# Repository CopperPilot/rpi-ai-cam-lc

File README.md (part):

# Compact CM5 AI Camera

Compute Module 5 6-layer carrier board (55x40 mm) with 12MP AI Camera rotated 90 deg on 8 mm spacers, 50 mm fold-under 15-pin FFC on CAM0, USB-C PD/flashing, 2x USB-A 2.0, full-size HDMI, and snap-fit two-part FDM enclosure assembled by Lion Circuits

Generated from photos with [rea-hardware](https://github.com/CopperPilot/rea-hardware): KiCad schematic and PCB, enclosure, manufacturing files, and a gated test suite.

| Front | Rear | Exploded |
|---|---|---|
|  |  |  |

**Build video:** [docs/build-video.mp4](docs/build-video.mp4). Assembly order and insertion paths come from `rea/spec.yaml`, the same ones the collision tests check.

## Verification

Verdict **PASS**: 45 pass, 3 warn, 0 fail, 0 error, 0 skipped (generated 2026-11-04T23:04:28Z).

| Gate | Status | Detail |
|---|---|---|
| `spec.valid` Scope contract rea/spec.yaml is complete and consistent | PASS | must_match=8, blocks=5, placements=17, purchased=6, enclosure_parts=4, assembly_steps=11, requirements=8, prompt_chars=9 |
| `inputs.present` Input images and prompt are inside the workspace | PASS | images=6 |
| `brand.clean` No third-party brand marks in names, silkscreen, case or docs | PASS | hits=0 |
| `scope.board_fits` Every board fits inside the product's rounded outline, inside its wall | PASS | boards=1 |
| `sourcing.bom` Every placed part has a live, in-stock part at the fab's parts source | PASS | placed_symbols=81, unique_parts=37, lion_in_house=3, bom_cost_inr=22308.98 |
| `kicad.erc` Schematic ERC: 0 errors | PASS | errors=0, warnings=0 |
| `kicad.drc` PCB DRC with schematic parity + zone refill: 0/0/0 | WARN | errors=0, warnings=300, unconnected=0, parity=0 |
| `kicad.rules` Project rules are no looser than the fab profile; nothing silenced | PASS | fab=lioncircuits, copper_layers=6, tracks=1093, vias=179 |
| `board.contract` Board outline, holes and user-facing parts match the spec | PASS | width_mm=55.0, height_mm=40.0 |
| `kicad.models` Every placed footprint has a 3D model on disk | PASS | lcsc_models_misplaced=0, footprints=88, missing=0, unresolved=0, tampered=0 |
| `kicad.refs` Modules with a verified reference symbol use it (no hand-drawn pinouts) | PASS |  |
| `board.antenna` A module's printed antenna sits at the board edge with nothing around it | PASS |  |
| `kicad.parts` Every part sits on the footprint of that exact LCSC part, with its real 3D model (no placeholders) | WARN | parts=81, lcsc_codes=34, wrong_footprint=0, placeholders=0 |
| `board.cable_pinout` Both ends of each board-to-board cable carry the same signal on each wire | PASS |  |
| `board.stackup` The board's layer count, thickness and stackup match the spec and the fab | PASS | stack_mm:main=1.65 |
| `board.high_speed` Declared high-speed groups (DDR, MIPI, USB) are routed, length-matched and on target impedance | PASS |  |
| `board.user_ports` Every receptacle a person plugs into sits behind a case opening | PASS | user_receptacles:main=4 |
| `board.cc_protection` USB-C CC lines are not clamped to VBUS by a rail-referenced ESD array | PASS |  |
| `board.ground_pins` No ground pin is left unconnected | PASS |  |
| `board.pd_autonomous` A USB-PD charging input negotiates with no processor running | PASS |  |
| `board.connector_mating` Every connector mates from a known side, toward its cable, with a clear mating zone in its footprint | PASS | connectors:main=13 |
| `board.height_zones` Parts under an overhead part stay below the zone's height limit | PASS |  |
| `board.port_facing` Every user-facing port's connector opens towards its case opening (3D model) | PASS |  |
| `review.design` Datasheet-level design review (CopperPilot validate): no open P0 or P1 findings | PASS |  |
| `mech.meshes` Enclosure parts exist, are closed solids, and fit the envelope | PASS |  |
| `mech.openings` Every front/rear/edge feature has an opening in the shell, at its size | PASS | features_tested=7 |
| `mech.assembly` Draft assembly: no collisions seated or along insertion paths | PASS | parts=11, pairs=55, sweep_hits=0, min_clearance_mm=0.0 |
| `mech.dfm` Each enclosure part is manufacturable by its process (walls, build size) | PASS |  |
| `fidelity.dims` Key proportions (bezel, edge and centre thickness, overall size) match the reference | PASS | overall_width=59.0, overall_height=44.0, overall_depth=27.5, edge_thickness=27.5, center_thickness=27.5, corner_radius=5 |
| `integration.assembly` Final assembly with the KiCad-exported PCBA: no collisions | PASS | parts=11, pairs=55, sweep_hits=0, min_clearance_mm=0.0 |
| `integration.cables` Every cable joins two real connectors and fits its route in every pose | PASS | cables=1 |
| `integration.actuators` Every button, crown, dial or sensor window physically works its part | PASS |  |
| `integration.ports` Every port opening has its connector right behind it (a plug can mate) | PASS | ports_tested=4 |
| `integration.mating` Every connector faces what mates with it, and every mounting hole sits on a boss (checked on the 3D models) | PASS | checked=9 |
| `integration.band` A wrist band closes round the wrist, its sensor faces the wrist, and a slide-on charger meets its contacts | PASS |  |
| `integration.retention` Every assembled part is held in place by something real (snap, clip, screw, adhesive, press fit, captured) | PASS |  |
| `integration.rf` A radio's antenna is not sealed inside metal (an RF window exists) | PASS |  |
| `integration.battery_fill` In a laptop- or tablet-sized product the battery fills the free space at its height | PASS |  |
| `integration.camera_view` Every camera sees out: its whole field of view clears the case | PASS |  |
| `fab.package` Gerbers, drill, BOM and CPL exist and agree with the PCB | WARN | bom_lines=34, placements=81, gerber_files=18 |
| `video.build` 3D build video exists and actually shows motion | PASS | seconds=48.0, frames=1440, moving_fraction=0.95 |
| `tests.integrity` Generated test suite is the rea template, unmodified | PASS |  |
| `fidelity.judge` Independent visual judge: renders match the reference photos | PASS | score=9.0, features=8, requirements_score=9 |
| `spec.locked` Scope contract unchanged since scope (or changes justified) | PASS | changed_keys=0 |
| `system.valid` System spec: modules, interfaces, power tree, assembly order are consistent | PASS |  |
| `system.modules` Every built module passes all of its own gates | PASS |  |
| `system.assembly` Modules do not collide with each other, seated or along system insertion paths | PASS |  |
| `system.cables` Every inter-module cable plugs into a real port on each module and is long enough | PASS |  |

Run them yourself: `pip install rea-hardware[video]` then `make test` (one pytest case per gate).

## Bill of materials

33 lines; full file: `fab/rpi-ai-cam-lc-bom.csv`.

| Designators | Part | LCSC |
|---|---|---|
| C1 | 2.2uF |  |
| C8,C10,C11,C12,C34 | 1uF |  |
| C2,C3,C19 | 22uF |  |
| C4,C5,C6,C7,C20,C21,C25,C33 | 100nF |  |
| C22,C23,C24 | 4.7nF |  |
| C26,C27,C28,C29,C30,C31 | 100uF |  |
| C9,C32 | 2.2uF |  |
| D1,D2,D3 | USBLC6-2SC6 |  |
| D5,D6,D7,D9,D10,D11 | TPD1E05U06DPYR |  |
| D12 | BAT54S |  |
| D4 | TVS2200DRVR |  |
| D8 | PESD3V3S1BLYL |  |
| J1 | USB4105-GF-A |  |
| J2,J3 | 629104190121 |  |
| J4 | 10029449-111RLF |  |
| J5 | SFW15R-1STE1LF |  |
| J6,J7 | 10164227-1001A1RLF |  |
| R1,R2,R16 | 43k |  |
| R6,R7,R10,R11 | 22k |  |
| R12 | 390k |  |
| R13 | 49.9k |  |
| R14 | 107k |  |
| R8,R9,R15,R20 | 100k |  |
| R5,R17,R18 | 1.33k |  |
| R19 | 6.8k |  |
| SP1,SP2,SP3,SP4 | 9774080243R |  |
| SP5,SP6,SP7,SP8 | 9774015960R |  |
| SW1 | PTS526SM15SMTR2LFS |  |
| SW2 | B3U-1000P |  |
| U1 | TPD12S016PWR |  |
| U2,U3 | AP2553W6-7 |  |
| U4,U5 | TPS259470ARPWR |  |
| U6 | TPD6S300ARUKR |  |

Off-board parts:

- **cm5**: Compute Module 5 with eMMC (any eMMC variant such as CM5104016 or CM5104032; bought outside Lion Circuits, excluded from the Lion PCBA BOM, and pressed into J6/J7 at final assembly)  (https://www.raspberrypi.com/products/compute-module-5/)
- **ai_camera**: 12 MP IMX500 Intelligent Vision Camera Module SC1174 (https://www.lioncircuits.com/parts)
- **m2_washers**: Eight flat M2 x 0.5 mm nylon washers (two per spacer, 1.0 mm stack height, OD 4.0 mm, ID 2.2 mm) placed atop SP1..SP4  (https://www.mcmaster.com/90295A080/)
- **camera_m2_screws**: Four Essentra M2 x 4 mm pan-head nylon screws fastening ai_camera through m2_washers into SP1..SP4 50M020040N003 (https://www.lioncircuits.com/parts)
- **m25_inserts**: Four M2.5 x 3.5 mm brass heat-set threaded inserts (OD 3.5 mm) pressed into back_shell corner bosses  (https://www.mcmaster.com/94180A321/)
- **m25_screws**: Four M2.5 x 8 mm pan-head machine screws passing from carrier top through SP5..SP8 and the module into m25_inserts  (https://www.mcmaster.com/92000A065/)

## Manufacture

Fab profile: `lioncircuits`, 6 layers, 1.6 mm. Upload `fab/*-gerbers.zip`, then the BOM and CPL CSVs for assembly. Print the enclosure STLs in `case/out/` (fdm).

## Rebuild

```
make all      # case, fab, renders, video, tests, README
make test     # gates only
```

## Scope

- In scope: camera lens window, power button, boot pinhole, USB-C power and flashing port, HDMI port, USB 2.0 Type-A host port 0, USB 2.0 Type-A host port 1, rear CM5 cooling vents
- Out of scope: tripod mount thread, external Wi-Fi u.FL antenna, SD card slot, 40-pin GPIO expansion header
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
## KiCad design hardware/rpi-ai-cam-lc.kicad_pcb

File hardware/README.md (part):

# Compact CM5 AI Camera Carrier (`hardware/rpi-ai-cam-lc`)

Generated from `rea/spec.yaml` by rea-hardware (Lion Circuits Custom tier fab rules, 6-layer 1.6 mm controlled-impedance stack-up, 55.0 x 40.0 mm board outline at origin, mounting holes), then completed and routed for the Compute Module 5 carrier.

## Programming and Debug Path (`decisions`)
- **eMMC Flashing (`rpiboot` over USB-C J1):**
  1. Press and hold recessed boot button `SW2` (Omron `B3U-1000P`, actuated via the front-shell pinhole `F3`), which pulls CM5 `nRPIBOOT` (`J6` pad 93) to `GND` (using CM5's internal `10 kOhm` pull-up to `+3V3` with no redundant external pull-up, and 3.3 V `PESD3V3S1BLYL` ESD TVS `D8` to `GND`).
  2. Connect a host PC to USB-C receptacle `J1` (`USB4105-GF-A`). `J1` supplies `VBUS_IN` (decoupled by `C1` = 2.2 uF and `C4` = 100 nF = `2.3 uF` nominal `cSink` <= 10 uF and protected by TI `TVS2200DRVR` 22 V flat-clamp unidirectional WSON-6 surge TVS `D4` with $V_{\text{RWM}} = 22\text{ V}$ for 20 V USB-C fault tolerance, $V_{\text{CLAMP}} = 27.2\text{ V}$ typ / $27.7\text{ V}$ max at 24 A and $27.6\text{ V}$ typ / $28.0\text{ V}$ max at 40 A $8/20\,\mu\text{s} \le +28\text{ V}$ abs max, and $V_F = -0.5\text{ V}$ typ) via wide `F.Cu` copper polygons, a dedicated 1 oz (`0.035 mm`) `In3.Cu` `VBUS_IN` plane, and 8 parallel `VBUS_IN` vias into two parallel TI `TPS259470ARPWR` active-current-limiting ideal-diode / OVP eFuses (`U4` primary, `U5` secondary; combined $R_{\text{ON(typ)}} = 14.15\text{ m}\Omega$ at $25^\circ\text{C}$ / $21.0\text{ m}\Omega$ max at $85^\circ\text{C}$, mirror-symmetric 9-via `U4.6`/`U5.6` output arrays, 1 oz `In3.Cu` `PWR_5V_PLANE` `/+5V`, and 5 parallel `+5V` vias with `0.50 mm` `B.Cu` bus bars at `J6` pads 77-87 -> `~2 mOhm` total PCB copper+via resistance and `~48 mV` typ / `~110 mV` max carrier drop at 3.0 A) driving all six CM5 `+5v_(Input)` pins (`J6` pads 77, 79, 81, 83, 85, 87). `U4` soft-starts via `C22` = 4.7 nF (`0.43 V/ms`, `~11.7 ms` ramp) so the CM5's internal PMIC input capacitance and carrier `+5V` bulk capacitance (`C30` = 100 uF, `C31` = 100 uF, `C9` = 2.2 uF, `C10..C12` = 3 x 1.0 uF) are isolated from `J1` at hot-plug while `U4`'s open-drain `AUXOFF` holds `U5` `EN/UVLO` low until `U4` achieves full gate overdrive, and `U5`'s open-drain `AUXOFF` (`U5.3`) connects to CM5 `PMIC_Enable` (`J6` pad 99, net `PMIC_ENABLE`) per TI Figure 8-18 to hold the CM5 PMIC in reset until both `U4` and `U5` have completed soft-start and reached full gate overdrive; `C23`/`C24` = 4.7 nF on `U4.10`/`U5.10` (`ITIMER`) set steady-state $t_{\text{ITIMER}} = 3.94\text{ ms}$. `J1` routes `USB2_P`/`USB2_N` directly (through inline ESD array `D1` at `J1`, with `D1` pin 5 on `VBUS_D1_CLAMP` locally decoupled to `GND` by `C25` = 100 nF) to CM5 USB 2.0 OTG (`J7` pads 5/3, CM5 pins 105/103), with `USB_OTG_ID` (`J7` pad 1, CM5 pin 101) left unconnected so the CM5's internal pull-up selects USB Device / `rpiboot` bootloader mode.
  3. The CM5 ROM bootloader enumerates over USB 2.0 OTG for `rpiboot` mass-storage flashing. During reset and `rpiboot`, `22 kOhm` pull-down `R10` holds `USB_VBUS_EN` (`J7` pad 11) at `0 V` so USB-A switches `U2` and `U3` remain disabled and isolated from `J1`.
- **UART0 Debug Console:**
  - Exposed on top-side 1.0 mm SMD test pads `TP1` (`UART0_TXD` / `GPIO14`, `J6` pad 55), `TP2` (`UART0_RXD` / `GPIO15`, `J6` pad 51), and `TP3` (`GND`), referenced to `+3V3` (`GPIO_VREF` on `J6` pad 78 strapped to `+3V3`).

## Component Voltage, Current, and Pinout Rating Checks
- **USB-C `cSink` Margin, Parallel `TPS259470ARPWR` Soft-Start / OVP Stage & Capacitor Voltage Ratings (>= 1.5x max rail voltage):**
  - `C1` (`CL21B225KBYNNWE`, LCSC `C6534398`, Samsung 2.2 uF 50 V 0805 X7R): rated **50 V** on `VBUS_IN` at `J1` (**1.79x margin** above `D4` `TVS2200DRVR` 28.0 V max 40 A 8/20 us clamping voltage and **2.38x margin** above continuous 21.0 V USB-C PD overvoltage faults).
  - `C9`, `C32` (`GRM188Z71E225KE43D`, 2.2 uF 0603 X7R): rated **25 V** on switched **5.0 V** (`+5V` bulk decoupling at `J6` and `PMIC_ENABLE` blanking filter `C32`, 5.0x margin).
  - `C4` (`GRM155R71H104KE14D`, 100 nF 0402 X7R): rated **50 V** on **5.0 V** (`VBUS_IN` high-frequency bypass at `J1`, 10.0x margin).
  - Total unswitched capacitance on `VBUS_IN` upstream of `U4`/`U5` is `C1` (2.2 uF) + `C4` (0.1 uF) = **2.3 uF nominal** (**2.53 uF max** at +10% tolerance, well below the `<= 10 uF` USB Type-C `cSink` limit).
  - **Parallel `TPS259470ARPWR` Ideal-Diode / OVP Stage (`U4`, `U5`, LCSC `C3662799`):** Configured per TI `TPS25947` Datasheet Section 8.2.7 / Figure 8-18 ("Two Devices Connected in Parallel for Higher Steady State Current Capability"):
    - Primary eFuse `U4` soft-starts via `C22` = `4.7 nF` 50 V X7R 0402 (`GRM155R71H472KA01D`, LCSC `C77024`) on pin 7 (`DVDT`), setting output ramp slew rate $\text{SR} = 2\,\mu\text{A} / 4.7\text{ nF} = 0.426\text{ V/ms}$ ($t_{\text{ramp}} \approx 11.7\text{ ms}$ to 5.0 V), limiting hot-plug charging current into the CM5 and carrier `+5V` capacitance (`C30` = 100 uF, `C31` = 100 uF, `C9` = 2.2 uF, `C10..C12` = 3 x 1.0 uF) while `U4` pin 3 (`AUXOFF`, open-drain) holds `U5` pin 1 (`EN/UVLO`, net `VBUS_U5_EN`) low.
    - Once `U4` completes inrush and reaches full HFET gate overdrive, `U4.3` (`AUXOFF`) goes high-Z and the divider `R15` = `100 kOhm` (referenced to upstream `VBUS_IN` to `VBUS_U5_EN`) / `R16` = `43 kOhm` (`VBUS_U5_EN` to `GND`) biases `U5.1` (`EN/UVLO`) to `1.50 V` at `5.0 V` (setting $V_{\text{IN(UVLO\_R)}} = 3.99\text{ V}$ and $V_{\text{IN(UVLO\_F)}} = 3.66\text{ V}$ without sensitivity to downstream `+5V` load droop), turning `U5` fully ON in parallel with `U4` for a combined $R_{\text{ON(typ)}} = 28.3\text{ m}\Omega / 2 = 14.15\text{ m}\Omega < 15\text{ m}\Omega$ (`42.5 mV < 0.05 V` drop at 3.0 A) and integrated reverse-current blocking; open-drain `U5` pin 3 (`AUXOFF`), `U4` pin 4 (`~{FLT}`), and `U5` pin 4 (`~{FLT}`) on net `VBUS_AUXOFF` feed CM5 `PMIC_Enable` (`J6` pad 99, net `PMIC_ENABLE`, internally pulled up to `+5V` via `100 kOhm` on CM5) through `R19` = `6.8 kOhm` (`RC0402FR-076K8L`, LCSC `C93940`), `C32` = `2.2 uF` 25 V X7R 0603 (`GRM188Z71E225KE43D`, LCSC `C415535` to `GND`, $C_{\text{eff}} \ge 1.85\,\mu\text{F}$ typ / $1.68\,\mu\text{F}$ min at 5 V bias and -10% tolerance, setting $\tau_{\text{fall}} = 14.0\text{ ms}$ nominal / $10.7\text{ ms}$ worst-case derated $> 2.7\times t_{\text{ITIMER}} = 3.94\text{ ms}$ so a $3.94\text{ ms}$ low pulse keeps `PMIC_ENABLE` $\ge 3.58\text{ V} \gg 2.0\text{ V}$ $V_{\text{IH(min)}}$, and $V_{\text{LOW}} = 0.37\text{ V} < 0.40\text{ V}$ $V_{\text{IL(max)}}$), external pull-up `R5` = `1.33 kOhm` (`RC0402FR-071K33L` from `+5V` to `VBUS_AUXOFF`), and dual series Schottky diode `D12` (`Rectron BAT54S`, LCSC `C408389`: Diode 1 Pin 1->3 from `VBUS_AUXOFF` to `PMIC_ENABLE` providing fast charge $\tau_{\text{rise}} = 2.88\text{ ms}$ nominal / $2.42\text{ ms}$ effective so `PMIC_ENABLE` slews $0.4\text{ V}\to 2.0\text{ V}$ in $1.12\text{ ms}$ and recharges $4.4\times$ faster than $\tau_{\text{fall}}$ without ratcheting while reverse-biasing when `VBUS_AUXOFF` is low, and Diode 2 Pin 3->2 from `PMIC_ENABLE` to `+5V` immediately discharging `C32` into `+5V` so `J6.99` is never back-driven on rapid `+5V` collapse) per TI Figure 8-18 ("To downstream enable").
    - Three-resistor divider `R12` = `390 kOhm` (`RC0402FR-07390KL`, LCSC `C163467`, $\ge 350\text{ k}\Omega$ per datasheet Note 2) / `R13` = `49.9 kOhm` (`RC0402FR-0749K9L`, LCSC `C137969`) / `R14` = `107 kOhm` (`RC0402FR-07107KL`, LCSC `C138070`) from `VBUS_IN` to `GND` sets `U4.1` (`EN/UVLO`) rising threshold to $1.20\text{ V} \times 546.9 / 156.9 = 4.18\text{ V}$ (falling $3.83\text{ V}$) and shared `U4.2`/`U5.2` (`OVLO`) rising threshold to $1.20\text{ V} \times 546.9 / 107 = 6.13\text{ V}$ typ ($5.83\text{ V}$ min $> 5.50\text{ V}$ USB-PD `vSafe5V` max, $6.45\text{ V}$ max; falling $5.62\text{ V}$ typ / $5.33\text{ V}$ min, disconnecting $> 6.1\text{ V}$ and 20 V USB-C faults).
    - `R17` and `R18` = `1.33 kOhm` 1% 0402 (`RC0402FR-071K33L`, LCSC `C276261`, $\ge 750\,\Omega$ UL2367 limit) on `U4.9` and `U5.9` (`ILM`) set $I_{\text{LIM(typ)}} = 2.504\text{ A}$ per channel ($5.00\text{ A}$ combined $\le \text{J1 } 5.0\text{ A}$ VBUS contact rating, $I_{\text{LIM(min)}} = 2.281\text{ A}$, $I_{\text{LIM(max)}} = 2.731\text{ A}$), ensuring neither eFuse reaches $I_{\text{LIM(min)}}$ under worst-case 60%/40% PCB passive current-sharing asymmetry up to $2.281\text{ A} / 0.60 = 3.80\text{ A}$ ($> 3.62\text{ A}$ worst-case system fault load / $3.26\text{ A}$ nominal full load) while active current-limit regulation equalizes sharing up to $5.0\text{ A}$, and `C23` and `C24` = `4.7 nF` 50 V X7R 0402 (`GRM155R71H472KA01D`, LCSC `C77024`) on `U4.10` (`VBUS_U4_ITIMER`) and `U5.10` (`VBUS_U5_ITIMER`) set steady-state transient overcurrent blanking to $t_{\text{ITIMER(typ)}} = 3.94\text{ ms}$ after start-up.
  - `C8`, `C10`, `C11`, `C12`, `C34` (`GRM155R61E105KE11J`, 1 uF 0402 X5R): rated **25 V** on switched **5.0 V** (`HDMI0_5V` output reservoir `C8` and `+5V` local input bypass `C10..C12` at `U2`, `U3`, and `U1` pin 11 `VCC5V`, 5.0x margin) and **3.3 V** (`U6.10` `VPWR` bypass `C34`, 7.6x margin).
  - `C26`..`C31` (`Kemet T520B107M010ATE070`, 100 uF 10 V 70 mOhm Case B 3528-21 `KO-CAP` polymer tantalum, LCSC `C600583`): rated **10 V** (90% recommended operating voltage up to **9.0 V** at $85^\circ\text{C}$ per Kemet T520 datasheet, 2.0x margin on **5.0 V**) with zero DC-bias derating. Two 100 uF polymer tantalum capacitors are placed on `USB0_VBUS` (`C26` at `(3.50, 31.50)`, `C27` at `(25.75, 35.15)`) and two on `USB1_VBUS` (`C28` at `(26.25, 29.55)`, `C29` at `(32.65, 26.80)`), providing **222 uF nominal / ~207.5 uF effective** (`>= 167.5 uF` worst-case at -20% tolerance) per USB 2.0 Type-A host port alongside `C2` and `C3` (`22 uF` 16 V X5R 0603 MLCC, `~7.5 uF` effective at 5 V bias), exceeding the `>= 120 uF` USB 2.0 Section 7.2.4.1 (Table 7-7, $C_{\text{PB}}$) requirement and limiting hot-plug droop into a 10 uF peripheral load to $\le 230\text{ mV} \le 330\text{ mV}$. Charging `207.5 uF` to 5.0 V at `U2`/`U3`'s current limit ($I_{\text{LIM(typ)}} = 0.615\text{ A}$, $I_{\text{LIM(min)}} = 0.56\text{ A}$) takes $1.69\text{ ms}$ typ ($1.85\text{ ms}$ at $0.56\text{ A}$), well within the `AP2553W6-7`'s $7\text{ ms}$ typical ($4\text{--}15\text{ ms}$) fault-blanking timer ($t_{\text{Blank}}$). Two additional 100 uF polymer tantalum capacitors (`C30` at `(32.50, 12.20)`, `C31` at `(32.50, 5.50)`) provide **205.2 uF nominal / ~203.5 uF effective** bulk storage on the switched `+5V` rail alongside `C9` (`2.2 uF`) and `C10..C12` (`3 x 1 uF`), adding only $86\text{ mA}$ during `U4`'s $0.43\text{ V/ms}$ soft-start ramp.
  - `C2`, `C3`, `C19` (`CL10A226MO7JZNC`, Samsung 22 uF 16 V 0603 X5R; alternate `CL10A226MP8NUNE` 10 V X5R 0603): rated **16 V** (or **10 V** alternate) on switched **5.0 V** (`USB0_VBUS` high-frequency bypass on `C2`, `USB1_VBUS` high-frequency bypass on `C3`, >=2.0x margin) and **3.3 V** (`+3V3` camera bulk decoupling at `J5` on `C19`, >=3.0x margin).
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
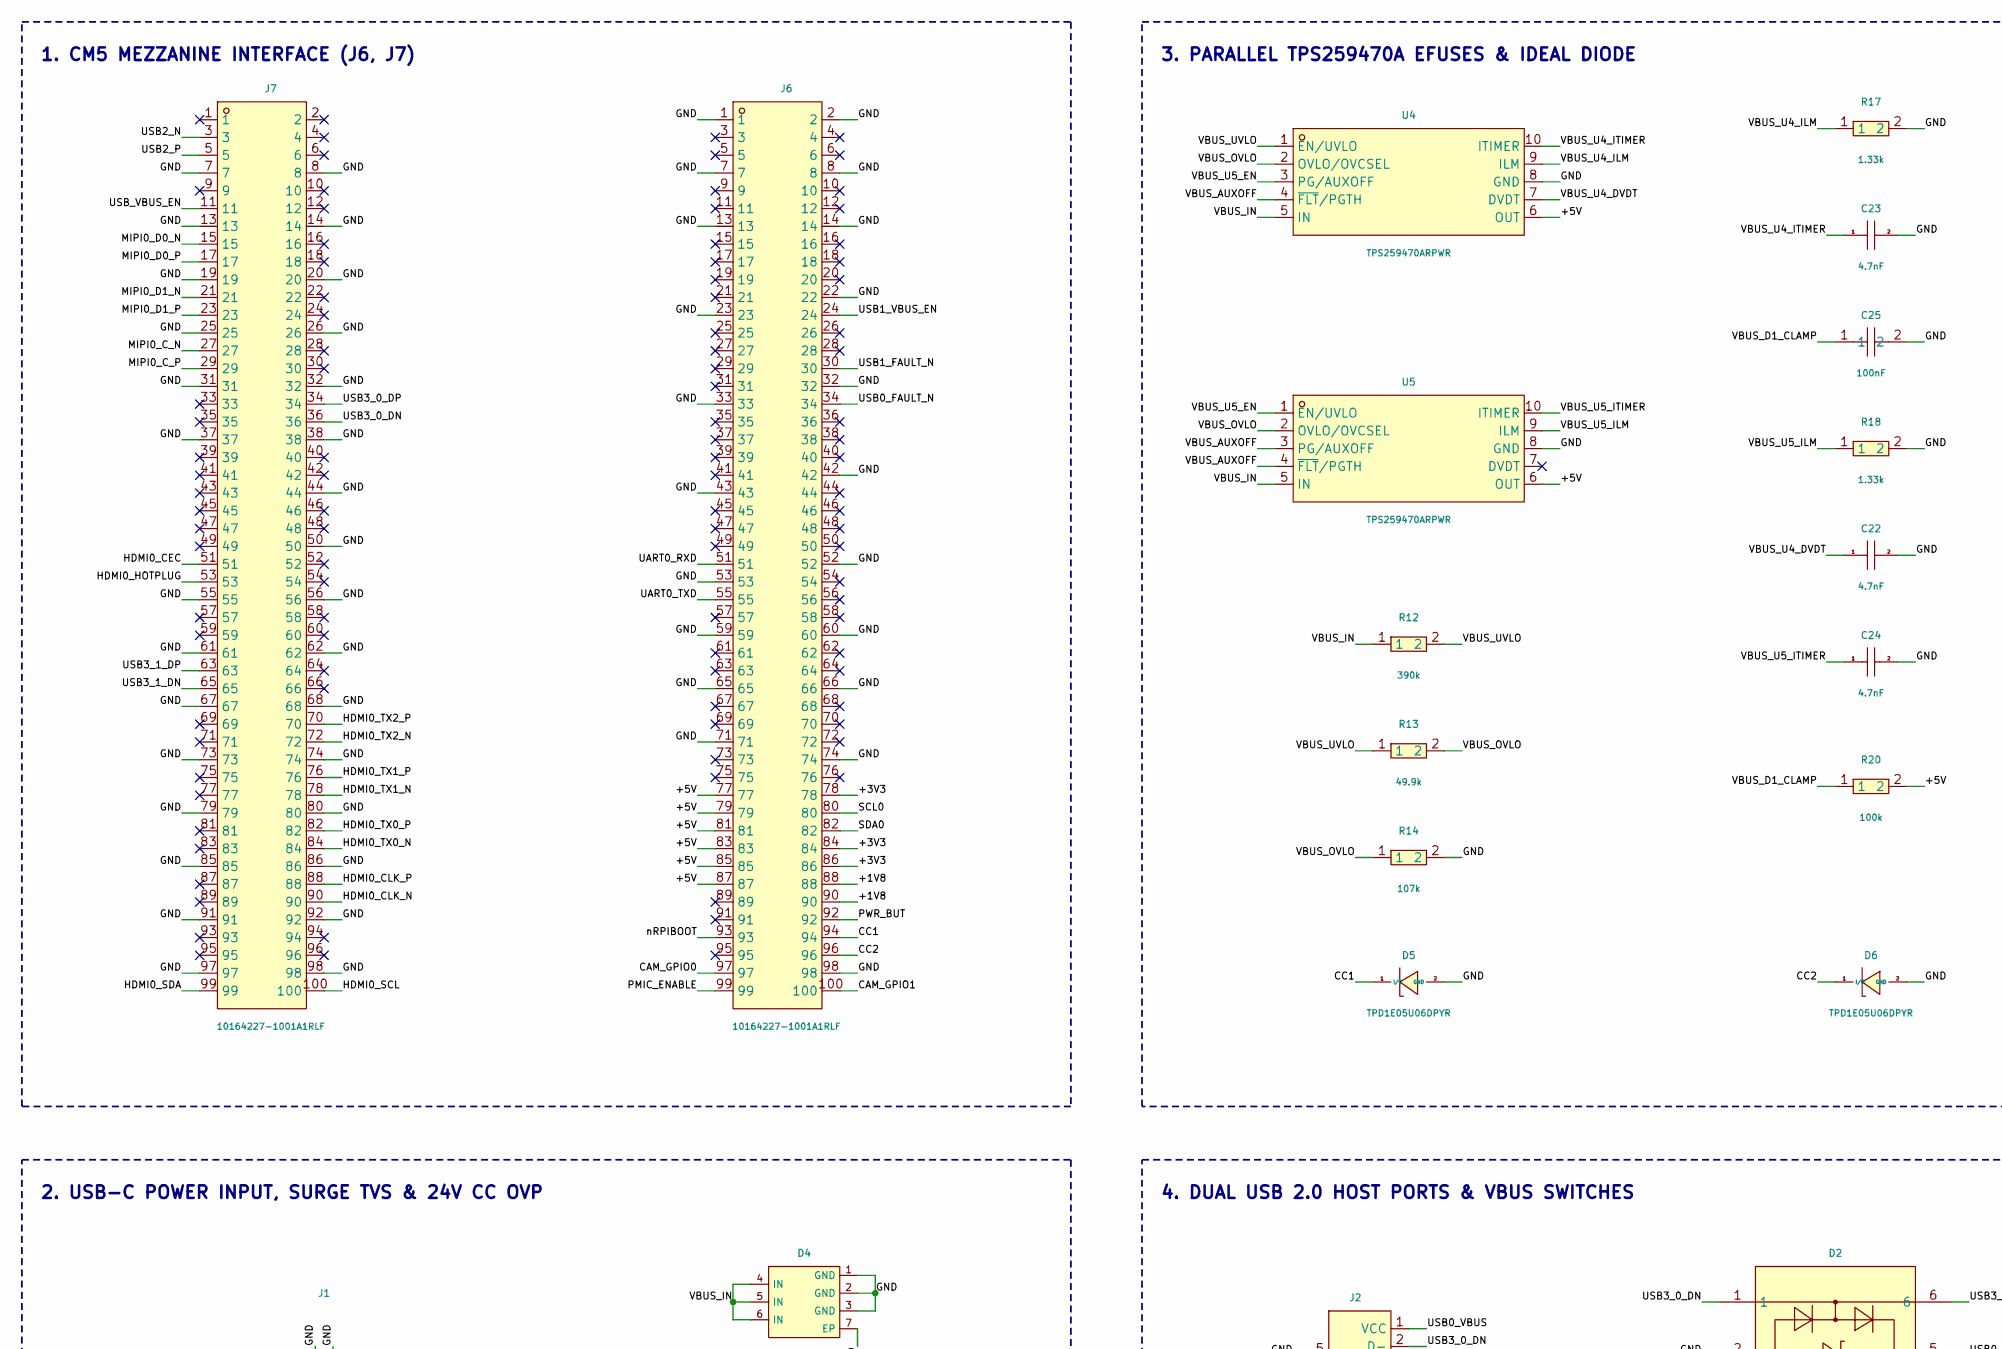
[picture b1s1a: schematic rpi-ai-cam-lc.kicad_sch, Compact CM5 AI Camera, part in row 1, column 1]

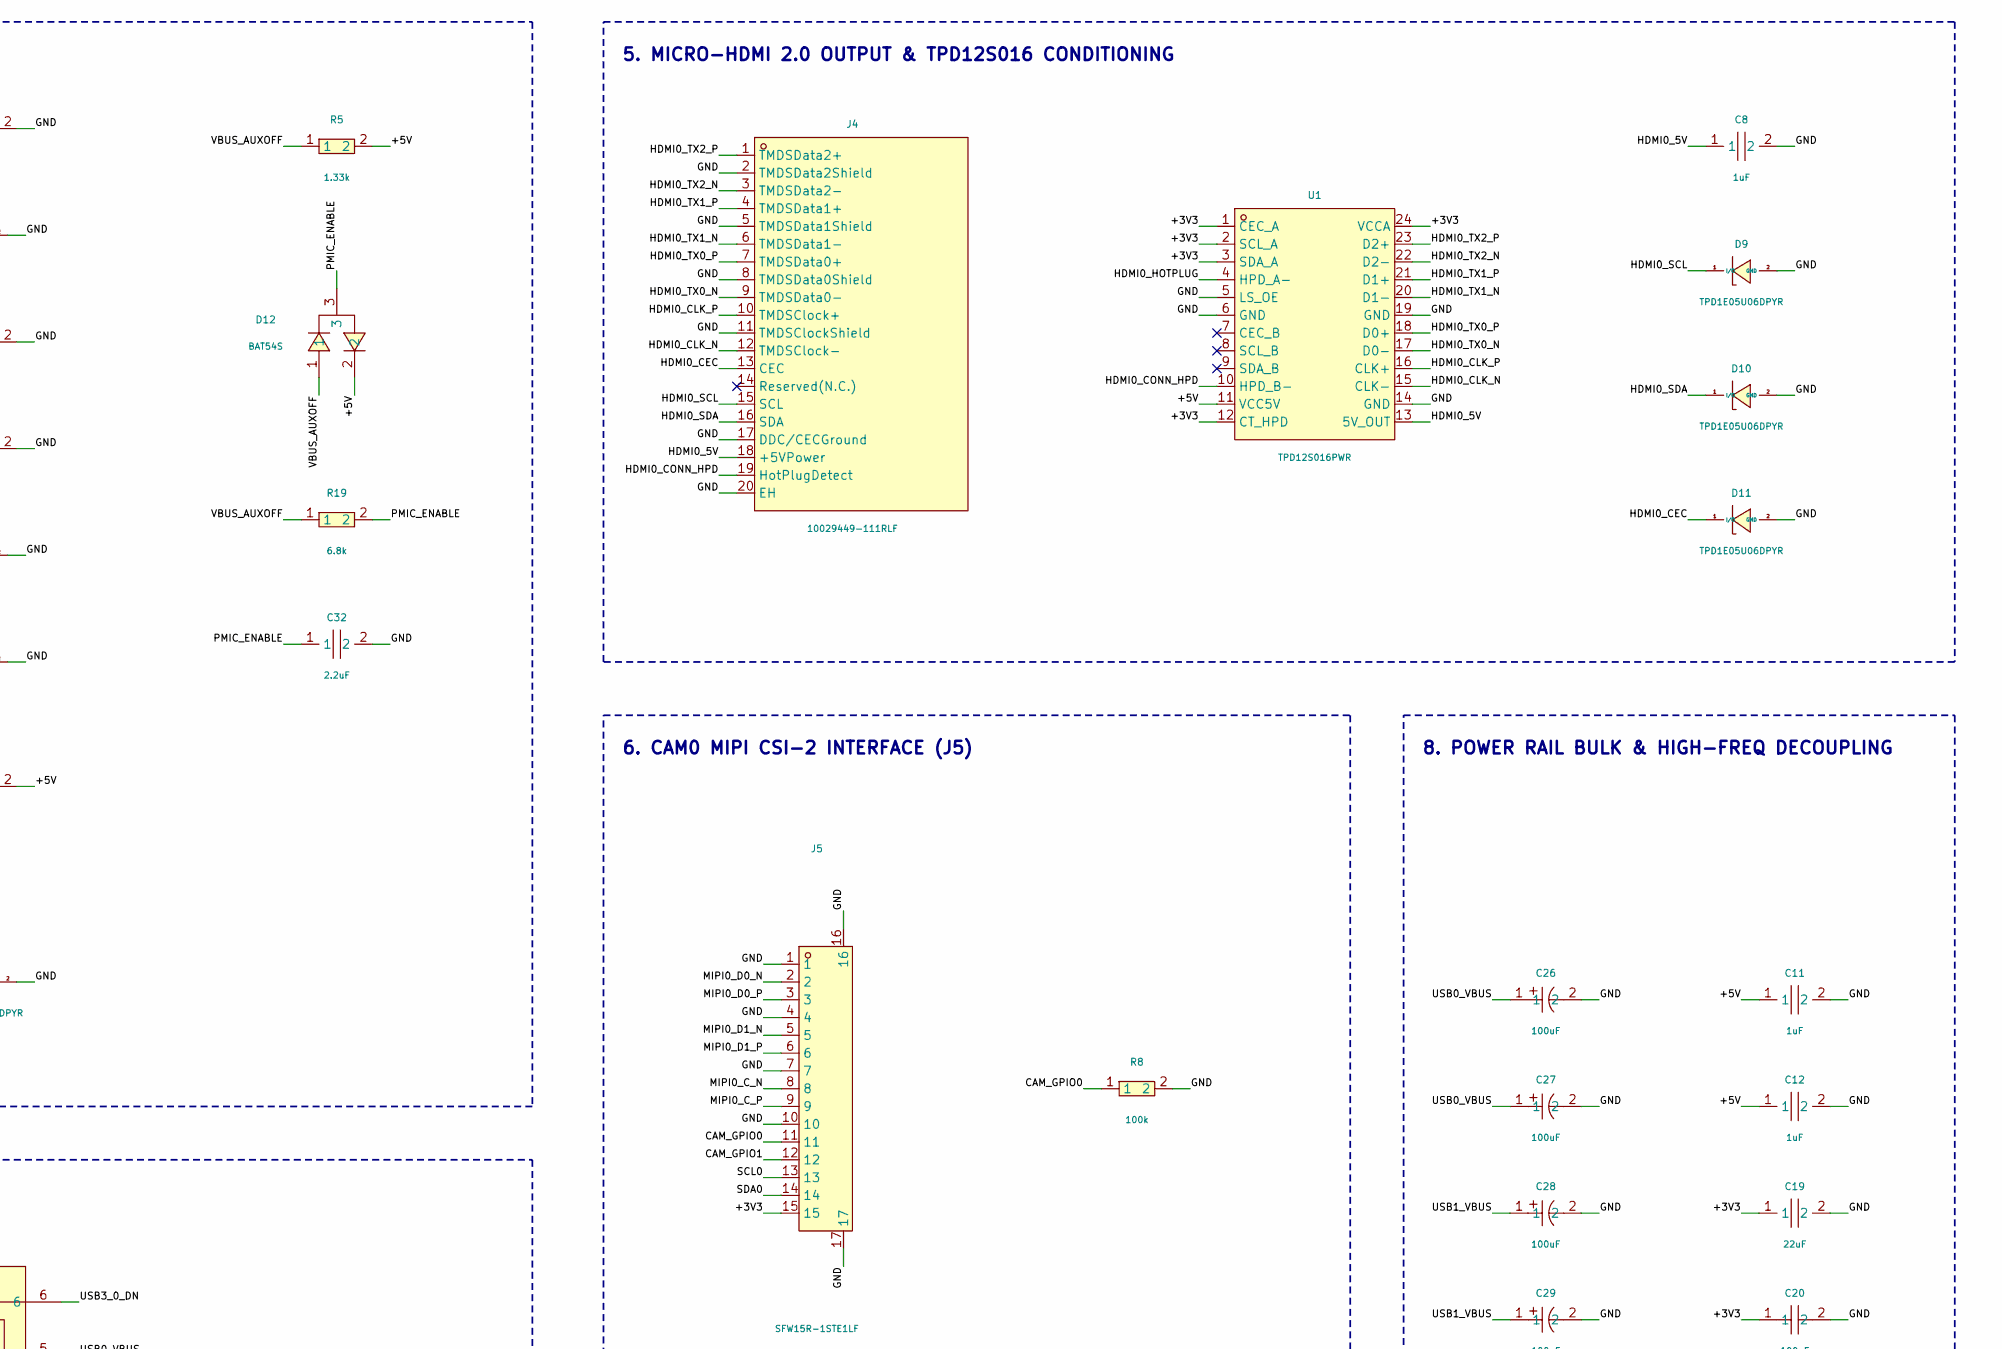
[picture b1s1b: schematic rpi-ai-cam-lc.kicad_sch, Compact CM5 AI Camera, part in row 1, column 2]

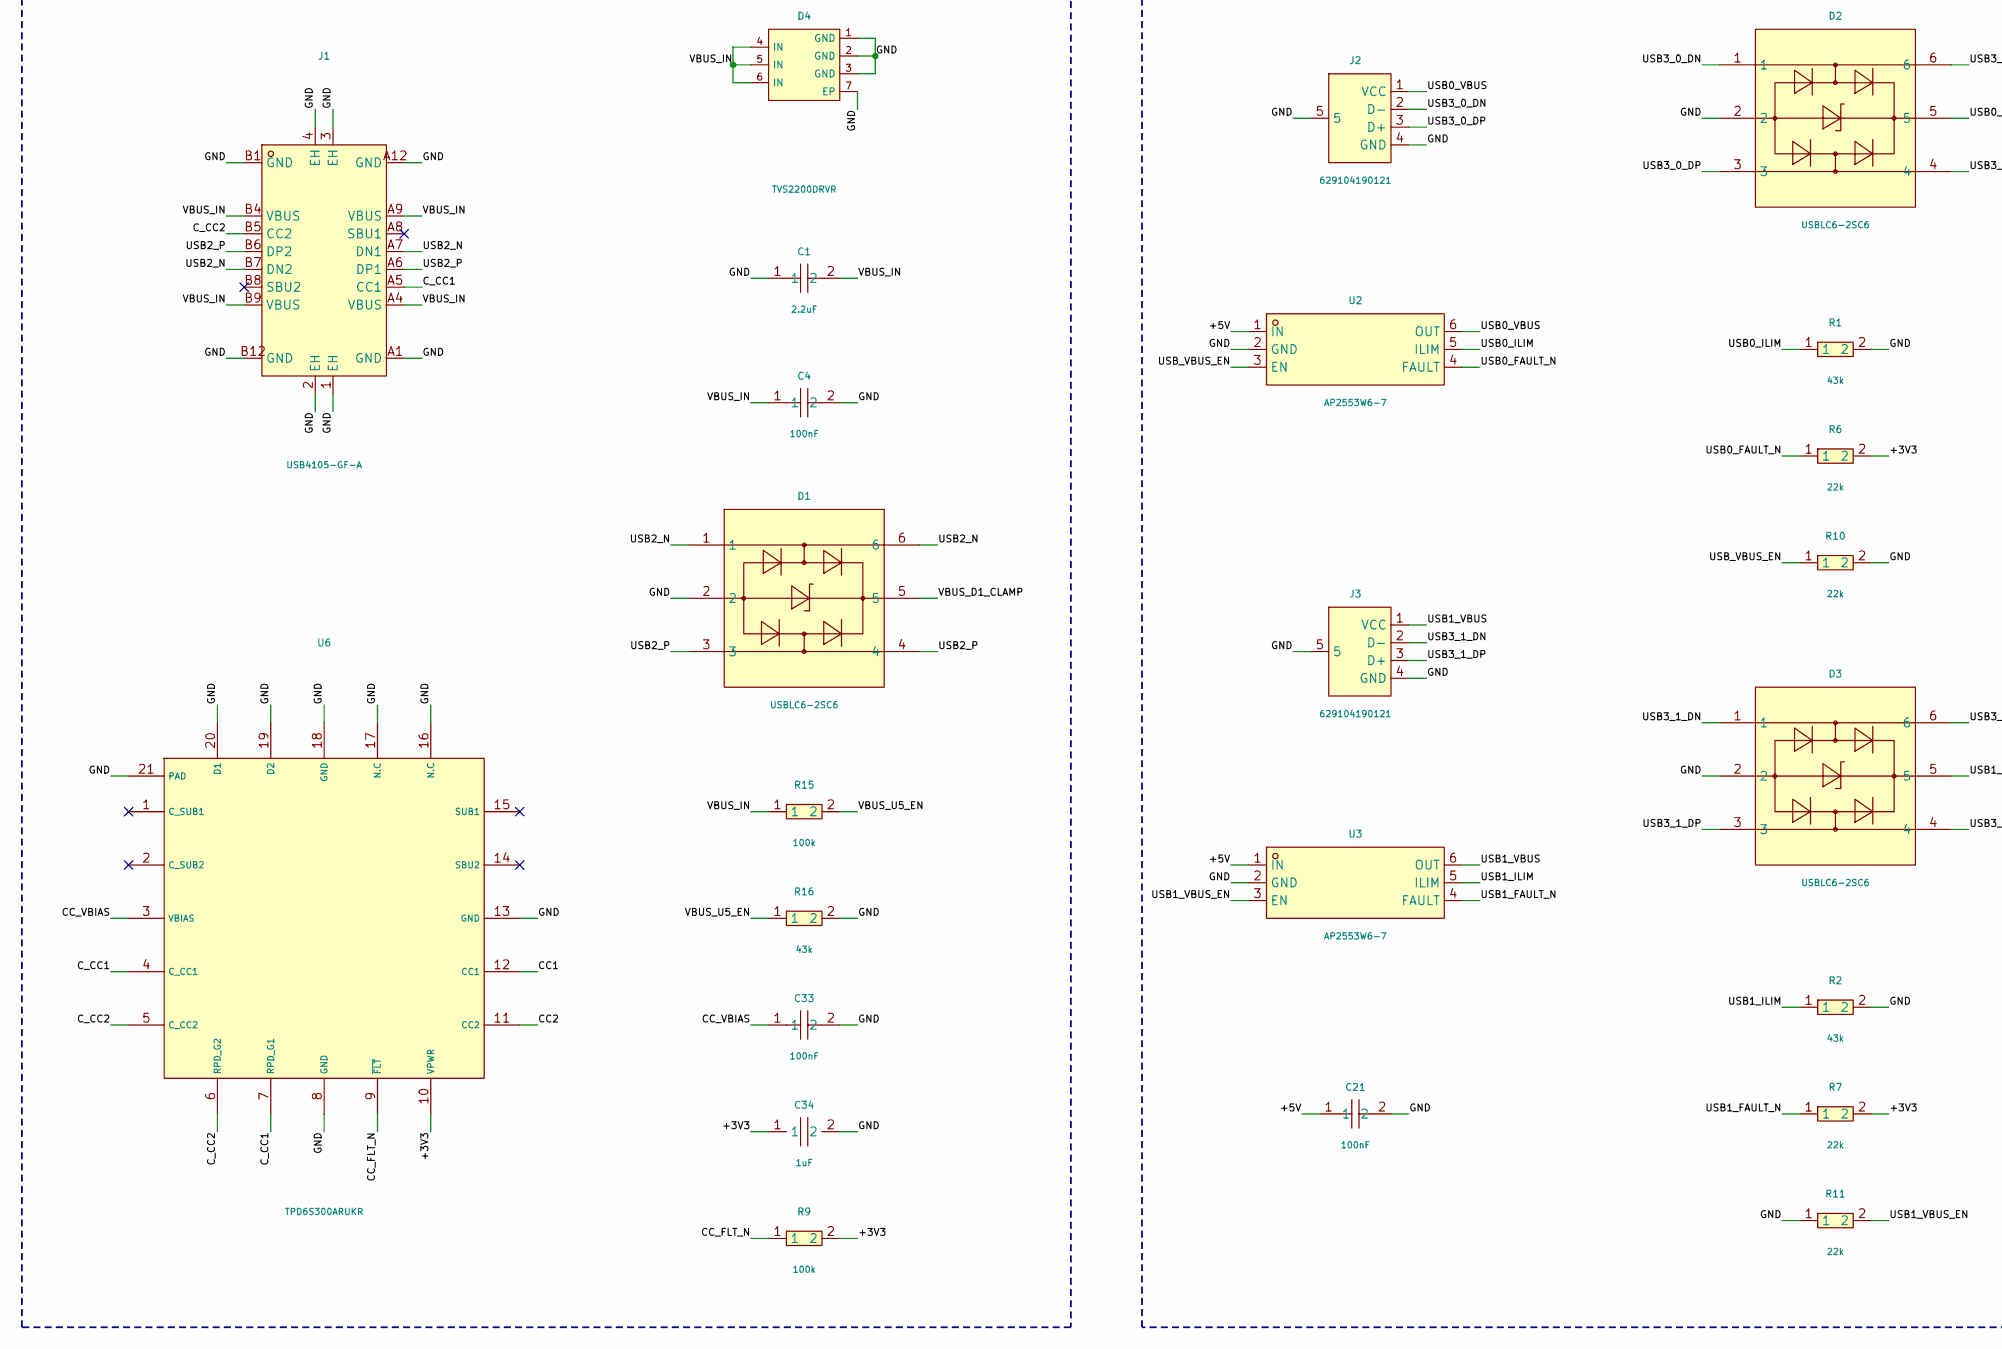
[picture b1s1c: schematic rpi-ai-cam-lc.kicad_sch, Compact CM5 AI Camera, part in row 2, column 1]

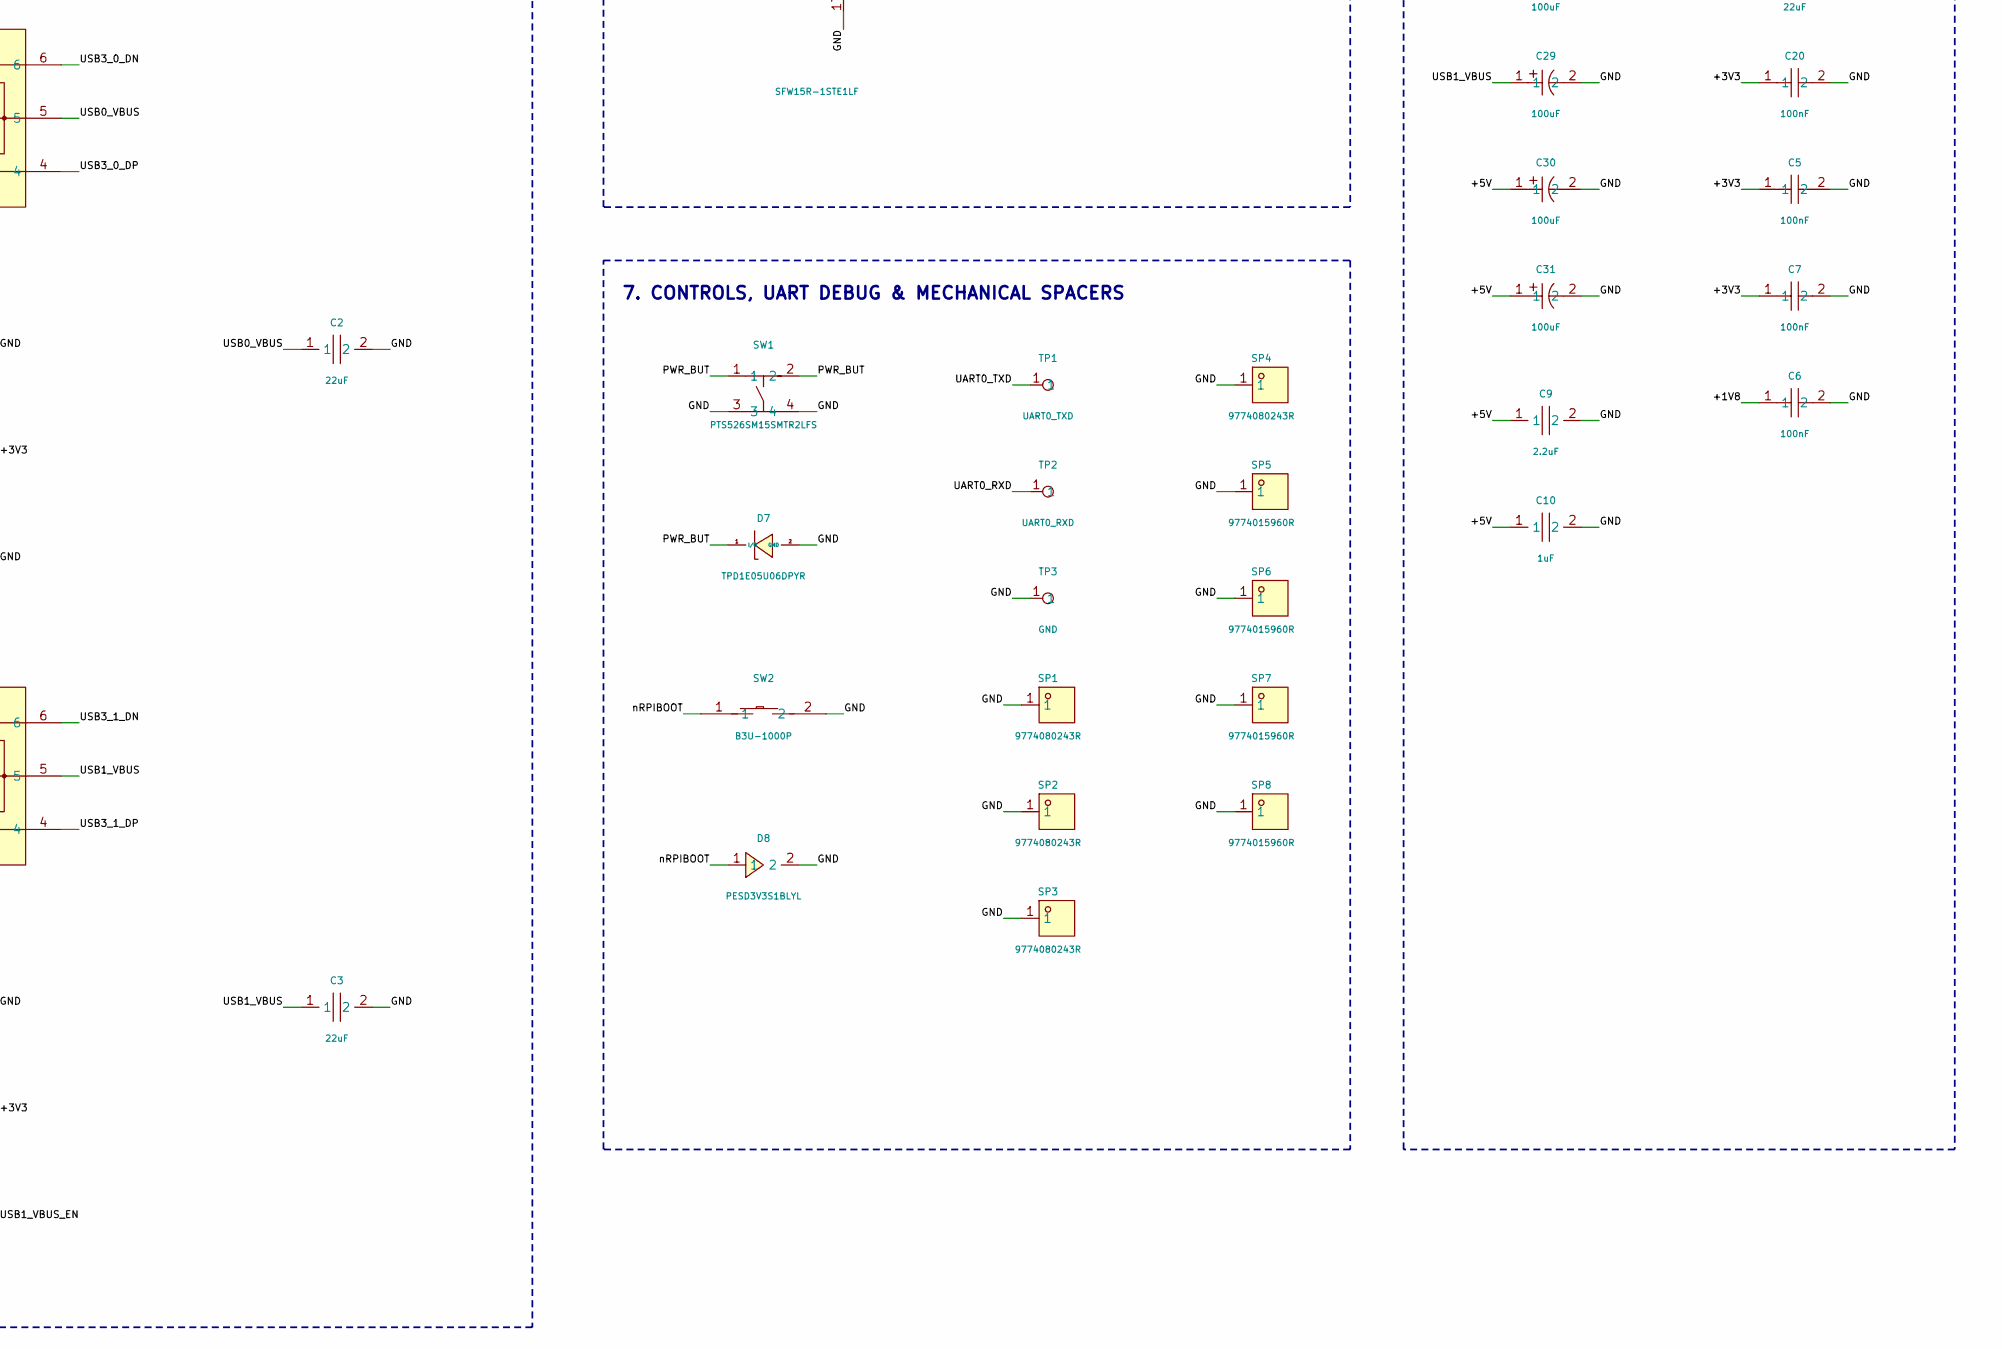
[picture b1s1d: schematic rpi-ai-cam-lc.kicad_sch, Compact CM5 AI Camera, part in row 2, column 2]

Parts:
C1: 2.2uF; C0805; MPN CL21B225KBYNNWE; LCSC C6534398
C2, C3, C19: 22uF; C0603; MPN CL10A226MO7JZNC; LCSC C2762594
C4, C5, C6, C7, C20, C21, C25, C33: 100nF; C0402; MPN GRM155R71H104KE14D; LCSC C77020
C8, C10, C11, C12, C34: 1uF; C0402; MPN GRM155R61E105KE11J; LCSC C77009
C9, C32: 2.2uF; C0603; MPN GRM188Z71E225KE43D; LCSC C415535
C22, C23, C24: 4.7nF; C0402; MPN GRM155R71H472KA01D; LCSC C77024
C26, C27, C28, C29, C30, C31: 100uF; CAP-SMD_L3.5-W2.8; MPN T520B107M010ATE070; LCSC C600583
D1, D2, D3: USBLC6-2SC6; SOT-23-6_L2.9-W1.6-P0.95-LS2.8-BL; MPN USBLC6-2SC6; LCSC C7519
D4: TVS2200DRVR; WSON-6_L2.0-W2.0-P0.65-TL-EP; MPN TVS2200DRVR; LCSC C523793
D5, D6, D7, D9, D10, D11: TPD1E05U06DPYR; X1SON-2_L1.0-W0.6-P0.65-RD-1; MPN TPD1E05U06DPYR; LCSC C436349
D8: PESD3V3S1BLYL; DFN1006-2L-BI; MPN PESD3V3S1BLYL; LCSC C552521
D12: BAT54S; SOT-23_L2.9-W1.3-P1.90-LS2.4-BR; MPN BAT54S; LCSC C408389
J1: USB4105-GF-A; TYPE-C-SMD_SBC-160S1A-20-S412; MPN USB4105GFA; LCSC C3020560
J2, J3: 629104190121; USB-A-SMD_629104190121; MPN 629104190121; LCSC C2890991
J4: 10029449-111RLF; HDMI-SMD_10029449-001RLF; MPN 10029449-111RLF; LCSC C427307
J5: SFW15R-1STE1LF; CONN-SMD_15P-P0.50_SFW15R-1STE1LF; MPN SFW15R-1STE1LF; LCSC C3168538
J6, J7: 10164227-1001A1RLF; CONN-SMD_100P-P0.40_10164227-1001A1RLF; MPN 10164227-1001A1RLF; LCSC C6782225
R1, R2, R16: 43k; R0402; MPN RC0402FR-0743KL; LCSC C185415
R5, R17, R18: 1.33k; R0402; MPN RC0402FR-071K33L; LCSC C276261
R6, R7, R10, R11: 22k; R0402; MPN RC0402FR-0722KL; LCSC C82868
R8, R9, R15, R20: 100k; R0402; MPN RC0402FR-07100KL; LCSC C60491
R12: 390k; R0402; MPN RC0402FR-07390KL; LCSC C163467
R13: 49.9k; R0402; MPN RC0402FR-0749K9L; LCSC C137969
R14: 107k; R0402; MPN RC0402FR-07107KL; LCSC C138070
R19: 6.8k; R0402; MPN RC0402FR-076K8L; LCSC C93940
SP1, SP2, SP3, SP4: 9774080243R; SMD-1_BD4.4-D2.8; MPN 9774080243R; LCSC C7495116
SP5, SP6, SP7, SP8: 9774015960R; SMD_BD6.0-D4.2; MPN 9774015960R; LCSC C27626588
SW1: PTS526SM15SMTR2LFS; SW-SMD_4P-L5.2-W5.2-P3.70-LS6.4; MPN PTS526SM15SMTR2LFS; LCSC C2689538
SW2: B3U-1000P; KEY-SMD_B3U-1000PM; MPN B3U-1000P; LCSC C231329
TP1: UART0_TXD; TestPoint_SMD_D1.0mm
TP2: UART0_RXD; TestPoint_SMD_D1.0mm
TP3: GND; TestPoint_SMD_D1.0mm
U1: TPD12S016PWR; TSSOP-24_L7.8-W4.4-P0.65-LS6.4-BL; MPN TPD12S016PWR; LCSC C201665
U2, U3: AP2553W6-7; SOT-26_L3.0-W1.6-P0.95-LS2.8-BL; MPN AP2553W6-7; LCSC C212302
U4, U5: TPS259470ARPWR; VQFN-10_L2.0-W2.0-P0.45-TL; MPN TPS259470ARPWR; LCSC C3662799
U6: TPD6S300ARUKR; WQFN-20_L3.0-W3.0-P0.40-TL-EP1.7; MPN TPD6S300ARUKR; LCSC C2876380

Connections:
/+1V8: C6.1, J6.88, J6.90
/+3V3: C5.1, C7.1, C19.1, C20.1, C34.1, J5.15, J6.78, J6.84, J6.86, R6.2, R7.2, R9.2, U1.1 (CEC_A), U1.2 (SCL_A), U1.3 (SDA_A), U1.12 (CT_HPD), U1.24 (VCCA), U6.10 (VPWR)
/+5V: C9.1, C10.1, C11.1, C12.1, C21.1, C30.1, C31.1, D12.2, J6.77, J6.79, J6.81, J6.83, J6.85, J6.87, R5.2, R20.2, U1.11 (VCC5V), U2.1 (IN), U3.1 (IN), U4.6 (OUT), U5.6 (OUT)
/CAM_GPIO0: J5.11, J6.97, R8.1
/CAM_GPIO1: J5.12, J6.100
/CC1: D5.1 (I/O), J6.94, U6.12 (CC1)
/CC2: D6.1 (I/O), J6.96, U6.11 (CC2)
/CC_FLT_N: R9.1, U6.9 (~FLT)
/CC_VBIAS: C33.1, U6.3 (VBIAS)
/C_CC1: J1.A5 (CC1), U6.4 (C_CC1), U6.7 (RPD_G1)
/C_CC2: J1.B5 (CC2), U6.5 (C_CC2), U6.6 (RPD_G2)
/GND: C1.1, C2.2, C3.2, C4.2, C5.2, C6.2, C7.2, C8.2, C9.2, C10.2, C11.2, C12.2, C19.2, C20.2, C21.2, C22.2, C23.2, C24.2, C25.2, C26.2, C27.2, C28.2, C29.2, C30.2, C31.2, C32.2, C33.2, C34.2, D1.2, D2.2, D3.2, D4.1 (GND), D4.2 (GND), D4.3 (GND), D4.7 (EP), D5.2 (GND), D6.2 (GND), D7.2 (GND), D8.2, D9.2 (GND), D10.2 (GND), D11.2 (GND), J1.1 (EH), J1.2 (EH), J1.3 (EH), J1.4 (EH), J1.A1 (GND), J1.A12 (GND), J1.B1 (GND), J1.B12 (GND), J2.4 (GND), J2.5, J3.4 (GND), J3.5, J4.2 (TMDSData2Shield), J4.5 (TMDSData1Shield), J4.8 (TMDSData0Shield), J4.11 (TMDSClockShield), J4.17 (DDC/CECGround), J4.20 (EH), J5.1, J5.4, J5.7, J5.10, J5.16, J5.17, J6.1, J6.2, J6.7, J6.8, J6.13, J6.14, J6.22, J6.23, J6.32, J6.33, J6.42, J6.43, J6.52, J6.53, J6.59, J6.60, J6.65, J6.66, J6.71, J6.74, J6.98, J7.7, J7.8, J7.13, J7.14, J7.19, J7.20, J7.25, J7.26, J7.31, J7.32, J7.37, J7.38, J7.44, J7.50, J7.55, J7.56, J7.61, J7.62, J7.67, J7.68, J7.73, J7.74, J7.79, J7.80, J7.85, J7.86, J7.91, J7.92, J7.97, J7.98, R1.2, R2.2, R8.2, R10.2, R11.1, R14.2, R16.2, R17.2, R18.2, SP1.1, SP2.1, SP3.1, SP4.1, SP5.1, SP6.1, SP7.1, SP8.1, SW1.3, SW1.4, SW2.2, TP3.1, U1.5 (LS_OE), U1.6 (GND), U1.14 (GND), U1.19 (GND), U2.2 (GND), U3.2 (GND), U4.8 (GND), U5.8 (GND), U6.8 (GND), U6.13 (GND), U6.16 (N.C), U6.17 (N.C), U6.18 (GND), U6.19 (D2), U6.20 (D1), U6.21 (PAD)
/HDMI0_5V: C8.1, J4.18 (+5VPower), U1.13 (5V_OUT)
/HDMI0_CEC: D11.1 (I/O), J4.13 (CEC), J7.51
/HDMI0_CLK_N: J4.12 (TMDSClock-), J7.90, U1.15 (CLK-)
/HDMI0_CLK_P: J4.10 (TMDSClock+), J7.88, U1.16 (CLK+)
/HDMI0_CONN_HPD: J4.19 (HotPlugDetect), U1.10 (HPD_B-)
/HDMI0_HOTPLUG: J7.53, U1.4 (HPD_A-)
/HDMI0_SCL: D9.1 (I/O), J4.15 (SCL), J7.100
/HDMI0_SDA: D10.1 (I/O), J4.16 (SDA), J7.99
/HDMI0_TX0_N: J4.9 (TMDSData0-), J7.84, U1.17 (D0-)
/HDMI0_TX0_P: J4.7 (TMDSData0+), J7.82, U1.18 (D0+)
/HDMI0_TX1_N: J4.6 (TMDSData1-), J7.78, U1.20 (D1-)
/HDMI0_TX1_P: J4.4 (TMDSData1+), J7.76, U1.21 (D1+)
/HDMI0_TX2_N: J4.3 (TMDSData2-), J7.72, U1.22 (D2-)
/HDMI0_TX2_P: J4.1 (TMDSData2+), J7.70, U1.23 (D2+)
/MIPI0_C_N: J5.8, J7.27
/MIPI0_C_P: J5.9, J7.29
/MIPI0_D0_N: J5.2, J7.15
/MIPI0_D0_P: J5.3, J7.17
/MIPI0_D1_N: J5.5, J7.21
/MIPI0_D1_P: J5.6, J7.23
/PMIC_ENABLE: C32.1, D12.3, J6.99, R19.2
/PWR_BUT: D7.1 (I/O), J6.92, SW1.1, SW1.2
/SCL0: J5.13, J6.80
/SDA0: J5.14, J6.82
/UART0_RXD: J6.51, TP2.1
/UART0_TXD: J6.55, TP1.1
/USB0_FAULT_N: J6.34, R6.1, U2.4 (FAULT)
/USB0_ILIM: R1.1, U2.5 (ILIM)
/USB0_VBUS: C2.1, C26.1, C27.1, D2.5, J2.1 (VCC), U2.6 (OUT)
/USB1_FAULT_N: J6.30, R7.1, U3.4 (FAULT)
/USB1_ILIM: R2.1, U3.5 (ILIM)
/USB1_VBUS: C3.1, C28.1, C29.1, D3.5, J3.1 (VCC), U3.6 (OUT)
/USB1_VBUS_EN: J6.24, R11.2, U3.3 (EN)
/USB2_N: D1.1, D1.6, J1.A7 (DN1), J1.B7 (DN2), J7.3
/USB2_P: D1.3, D1.4, J1.A6 (DP1), J1.B6 (DP2), J7.5
/USB3_0_DN: D2.1, D2.6, J2.2 (D-), J7.36
/USB3_0_DP: D2.3, D2.4, J2.3 (D+), J7.34
/USB3_1_DN: D3.1, D3.6, J3.2 (D-), J7.65
/USB3_1_DP: D3.3, D3.4, J3.3 (D+), J7.63
/USB_VBUS_EN: J7.11, R10.1, U2.3 (EN)
/VBUS_AUXOFF: D12.1, R5.1, R19.1, U4.4 (~FLT/PGTH), U5.3 (PG/AUXOFF), U5.4 (~FLT/PGTH)
/VBUS_D1_CLAMP: C25.1, D1.5, R20.1
/VBUS_IN: C1.2, C4.1, D4.4 (IN), D4.5 (IN), D4.6 (IN), J1.A4 (VBUS), J1.A9 (VBUS), J1.B4 (VBUS), J1.B9 (VBUS), R12.1, R15.1, U4.5 (IN), U5.5 (IN)
/VBUS_OVLO: R13.2, R14.1, U4.2 (OVLO/OVCSEL), U5.2 (OVLO/OVCSEL)
/VBUS_U4_DVDT: C22.1, U4.7 (DVDT)
/VBUS_U4_ILM: R17.1, U4.9 (ILM)
/VBUS_U4_ITIMER: C23.1, U4.10 (ITIMER)
/VBUS_U5_EN: R15.2, R16.1, U4.3 (PG/AUXOFF), U5.1 (EN/UVLO)
/VBUS_U5_ILM: R18.1, U5.9 (ILM)
/VBUS_U5_ITIMER: C24.1, U5.10 (ITIMER)
/VBUS_UVLO: R12.2, R13.1, U4.1 (EN/UVLO)
/nRPIBOOT: D8.1, J6.93, SW2.1

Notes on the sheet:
1. CM5 MEZZANINE INTERFACE (J6, J7)
2. USB-C POWER INPUT, SURGE TVS & 24V CC OVP
3. PARALLEL TPS259470A EFUSES & IDEAL DIODE
4. DUAL USB 2.0 HOST PORTS & VBUS SWITCHES
5. MICRO-HDMI 2.0 OUTPUT & TPD12S016 CONDITIONING
6. CAM0 MIPI CSI-2 INTERFACE (J5)
7. CONTROLS, UART DEBUG & MECHANICAL SPACERS
8. POWER RAIL BULK & HIGH-FREQ DECOUPLING
